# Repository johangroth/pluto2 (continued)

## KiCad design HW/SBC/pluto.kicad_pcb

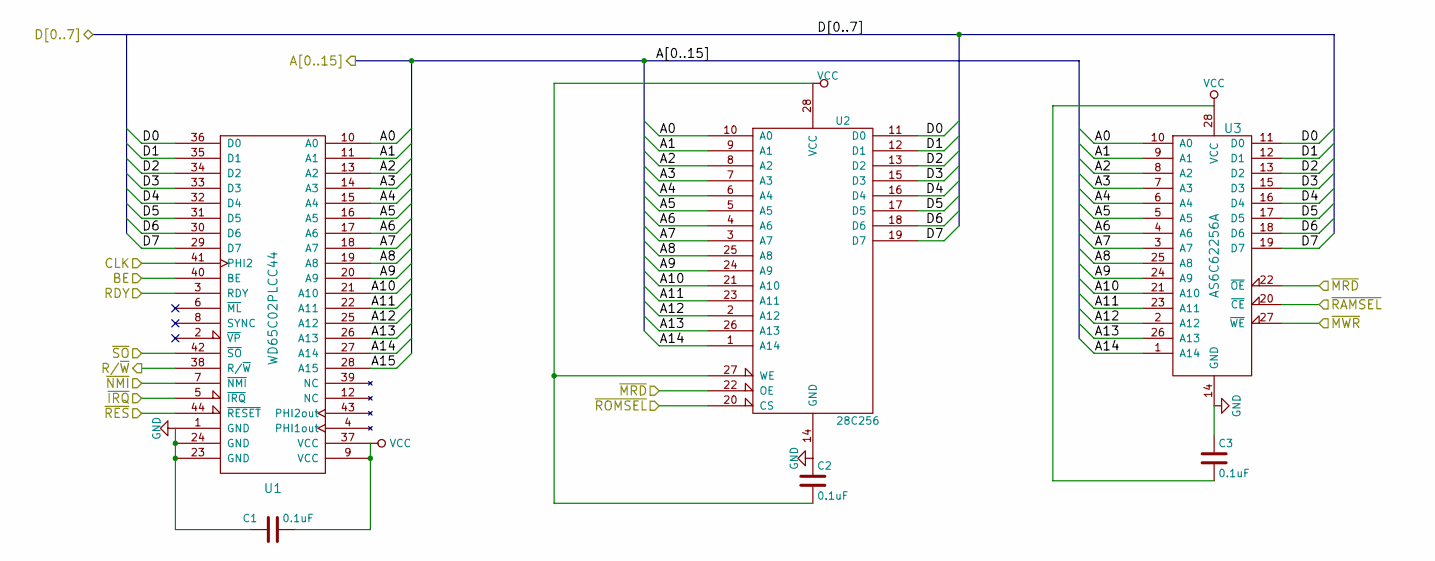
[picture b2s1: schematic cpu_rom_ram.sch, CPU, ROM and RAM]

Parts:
C1, C2, C3: 0.1uF; C_Disc_D4.7mm_W2.5mm_P5.00mm
U1: WD65C02PLCC44; PLCC-44_THT-Socket
U2: 28C256; DIP-28_W15.24mm_Socket
U3: AS6C62256A; DIP-28_W15.24mm_Socket

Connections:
/16bit IDE interface/A0: U1.10 (A0), U2.10 (A0), U3.10 (A0); also elsewhere on the board
/16bit IDE interface/A1: U1.11 (A1), U2.9 (A1), U3.9 (A1); also elsewhere on the board
/16bit IDE interface/A2: U1.13 (A2), U2.8 (A2), U3.8 (A2); also elsewhere on the board
/16bit IDE interface/D0: U1.36 (D0), U2.11 (D0), U3.11 (D0); also elsewhere on the board
/16bit IDE interface/D1: U1.35 (D1), U2.12 (D1), U3.12 (D1); also elsewhere on the board
/16bit IDE interface/D2: U1.34 (D2), U2.13 (D2), U3.13 (D2); also elsewhere on the board
/16bit IDE interface/D3: U1.33 (D3), U2.15 (D3), U3.15 (D3); also elsewhere on the board
/16bit IDE interface/D4: U1.32 (D4), U2.16 (D4), U3.16 (D4); also elsewhere on the board
/16bit IDE interface/D5: U1.31 (D5), U2.17 (D5), U3.17 (D5); also elsewhere on the board
/16bit IDE interface/D6: U1.30 (D6), U2.18 (D6), U3.18 (D6); also elsewhere on the board
/16bit IDE interface/D7: U1.29 (D7), U2.19 (D7), U3.19 (D7); also elsewhere on the board
/16bit IDE interface/~IRQ: U1.5 (~IRQ); also elsewhere on the board
/Address decoding and support section/A3: U1.14 (A3), U2.7 (A3), U3.7 (A3); also elsewhere on the board
/Address decoding and support section/A5: U1.16 (A5), U2.5 (A5), U3.5 (A5); also elsewhere on the board
/Address decoding and support section/A6: U1.17 (A6), U2.4 (A6), U3.4 (A6); also elsewhere on the board
/Address decoding and support section/A7: U1.18 (A7), U2.3 (A7), U3.3 (A7); also elsewhere on the board
/Address decoding and support section/A8: U1.19 (A8), U2.25 (A8), U3.25 (A8); also elsewhere on the board
/Address decoding and support section/A9: U1.20 (A9), U2.24 (A9), U3.24 (A9); also elsewhere on the board
/Address decoding and support section/A10: U1.21 (A10), U2.21 (A10), U3.21 (A10); also elsewhere on the board
/Address decoding and support section/A11: U1.22 (A11), U2.23 (A11), U3.23 (A11); also elsewhere on the board
/Address decoding and support section/A12: U1.25 (A12), U2.2 (A12), U3.2 (A12); also elsewhere on the board
/Address decoding and support section/A13: U1.26 (A13), U2.26 (A13), U3.26 (A13); also elsewhere on the board
/Address decoding and support section/A14: U1.27 (A14), U2.1 (A14), U3.1 (A14); also elsewhere on the board
/Address decoding and support section/A15: U1.28 (A15); also elsewhere on the board
/Address decoding and support section/BE: U1.40 (BE); also elsewhere on the board
/Address decoding and support section/CLK: U1.41 (PHI2); also elsewhere on the board
/Address decoding and support section/R/~W: U1.38 (R/~W); also elsewhere on the board
/Address decoding and support section/RDY: U1.3 (RDY); also elsewhere on the board
/Address decoding and support section/~MRD: U2.22 (OE), U3.22 (~OE); also elsewhere on the board
/Address decoding and support section/~MWR: U3.27 (~WE); also elsewhere on the board
/Address decoding and support section/~NMI: U1.7 (~NMI); also elsewhere on the board
/Address decoding and support section/~RAMSEL: U3.20 (~CE); also elsewhere on the board
/Address decoding and support section/~ROMSEL: U2.20 (CS); also elsewhere on the board
/Address decoding and support section/~SO: U1.42 (~SO); also elsewhere on the board
/CPU, ROM and RAM/A4: U1.15 (A4), U2.6 (A4), U3.6 (A4); also elsewhere on the board

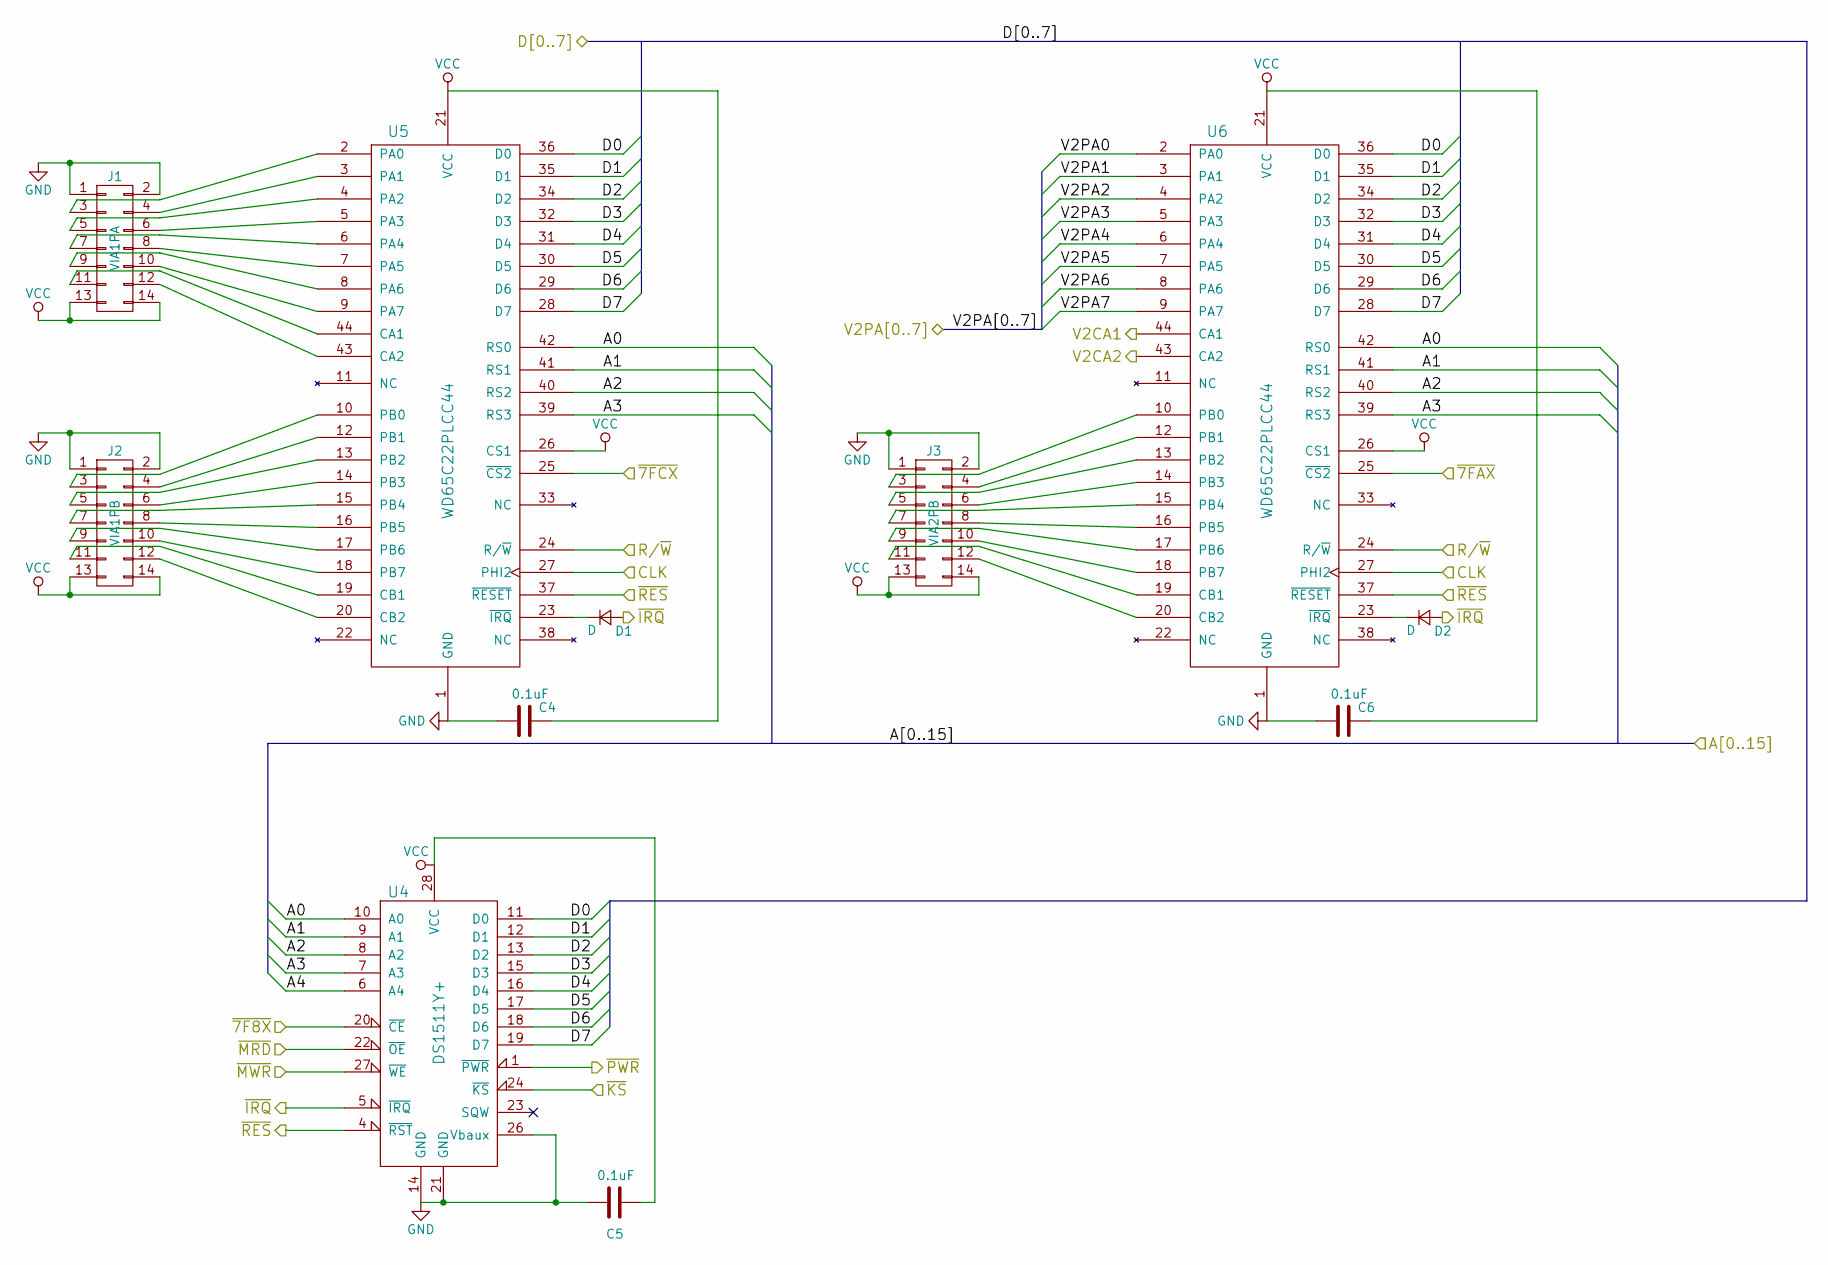
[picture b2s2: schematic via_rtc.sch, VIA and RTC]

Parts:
C4, C5, C6: 0.1uF; C_Disc_D4.7mm_W2.5mm_P5.00mm
D1, D2: D; D_DO-35_SOD27_P7.62mm_Horizontal
J1: VIA1PA; IDC-Header_2x07_Pitch2.54mm_Straight
J2: VIA1PB; IDC-Header_2x07_Pitch2.54mm_Straight
J3: VIA2PB; IDC-Header_2x07_Pitch2.54mm_Straight
U4: DS1511Y+; DIP-28_W15.24mm_Socket
U5, U6: WD65C22PLCC44; PLCC-44_THT-Socket

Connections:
/16bit IDE interface/A0: U4.10 (A0), U5.42 (RS0), U6.42 (RS0); also elsewhere on the board
/16bit IDE interface/A1: U4.9 (A1), U5.41 (RS1), U6.41 (RS1); also elsewhere on the board
/16bit IDE interface/A2: U4.8 (A2), U5.40 (RS2), U6.40 (RS2); also elsewhere on the board
/16bit IDE interface/D0: U4.11 (D0), U5.36 (D0), U6.36 (D0); also elsewhere on the board
/16bit IDE interface/D1: U4.12 (D1), U5.35 (D1), U6.35 (D1); also elsewhere on the board
/16bit IDE interface/D2: U4.13 (D2), U5.34 (D2), U6.34 (D2); also elsewhere on the board
/16bit IDE interface/D3: U4.15 (D3), U5.32 (D3), U6.32 (D3); also elsewhere on the board
/16bit IDE interface/D4: U4.16 (D4), U5.31 (D4), U6.31 (D4); also elsewhere on the board
/16bit IDE interface/D5: U4.17 (D5), U5.30 (D5), U6.30 (D5); also elsewhere on the board
/16bit IDE interface/D6: U4.18 (D6), U5.29 (D6), U6.29 (D6); also elsewhere on the board
/16bit IDE interface/D7: U4.19 (D7), U5.28 (D7), U6.28 (D7); also elsewhere on the board
/16bit IDE interface/~IRQ: D1.2 (A), D2.2 (A), U4.5 (~IRQ); also elsewhere on the board
/Address decoding and support section/A3: U4.7 (A3), U5.39 (RS3), U6.39 (RS3); also elsewhere on the board
/Address decoding and support section/CLK: U5.27 (PHI2), U6.27 (PHI2); also elsewhere on the board
/Address decoding and support section/R/~W: U5.24 (R/~W), U6.24 (R/~W); also elsewhere on the board
/Address decoding and support section/~7F8X: U4.20 (~CE); also elsewhere on the board
/Address decoding and support section/~7FAX: U6.25 (~CS2); also elsewhere on the board
/Address decoding and support section/~7FCX: U5.25 (~CS2); also elsewhere on the board
/Address decoding and support section/~KS: U4.24 (~KS); also elsewhere on the board
/Address decoding and support section/~MRD: U4.22 (~OE); also elsewhere on the board
/Address decoding and support section/~MWR: U4.27 (~WE); also elsewhere on the board
/Address decoding and support section/~PWR: U4.1 (~PWR); also elsewhere on the board
/CPU, ROM and RAM/A4: U4.6 (A4); also elsewhere on the board
unnamed: D1.1 (K), U5.23 (~IRQ)
unnamed: D2.1 (K), U6.23 (~IRQ)
unnamed: J1.3, U5.2 (PA0)
unnamed: J1.4, U5.3 (PA1)
unnamed: J1.5, U5.4 (PA2)
unnamed: J1.6, U5.5 (PA3)
unnamed: J1.7, U5.6 (PA4)
unnamed: J1.8, U5.7 (PA5)
unnamed: J1.9, U5.8 (PA6)
unnamed: J1.10, U5.9 (PA7)
unnamed: J1.11, U5.44 (CA1)
unnamed: J1.12, U5.43 (CA2)
unnamed: J2.3, U5.10 (PB0)
unnamed: J2.4, U5.12 (PB1)
unnamed: J2.5, U5.13 (PB2)
unnamed: J2.6, U5.14 (PB3)
unnamed: J2.7, U5.15 (PB4)
unnamed: J2.8, U5.16 (PB5)
unnamed: J2.9, U5.17 (PB6)
unnamed: J2.10, U5.18 (PB7)
unnamed: J2.11, U5.19 (CB1)
unnamed: J2.12, U5.20 (CB2)
unnamed: J3.3, U6.10 (PB0)
unnamed: J3.4, U6.12 (PB1)
unnamed: J3.5, U6.13 (PB2)
unnamed: J3.6, U6.14 (PB3)
unnamed: J3.7, U6.15 (PB4)
unnamed: J3.8, U6.16 (PB5)
unnamed: J3.9, U6.17 (PB6)
unnamed: J3.10, U6.18 (PB7)
unnamed: J3.11, U6.19 (CB1)
unnamed: J3.12, U6.20 (CB2)
unnamed 114: U6.2 (PA0); also elsewhere on the board
unnamed 115: U6.3 (PA1); also elsewhere on the board
unnamed 116: U6.4 (PA2); also elsewhere on the board
unnamed 117: U6.5 (PA3); also elsewhere on the board
unnamed 118: U6.6 (PA4); also elsewhere on the board
unnamed 119: U6.7 (PA5); also elsewhere on the board
unnamed 120: U6.8 (PA6); also elsewhere on the board
unnamed 121: U6.9 (PA7); also elsewhere on the board
unnamed 122: U6.44 (CA1); also elsewhere on the board
unnamed 123: U6.43 (CA2); also elsewhere on the board

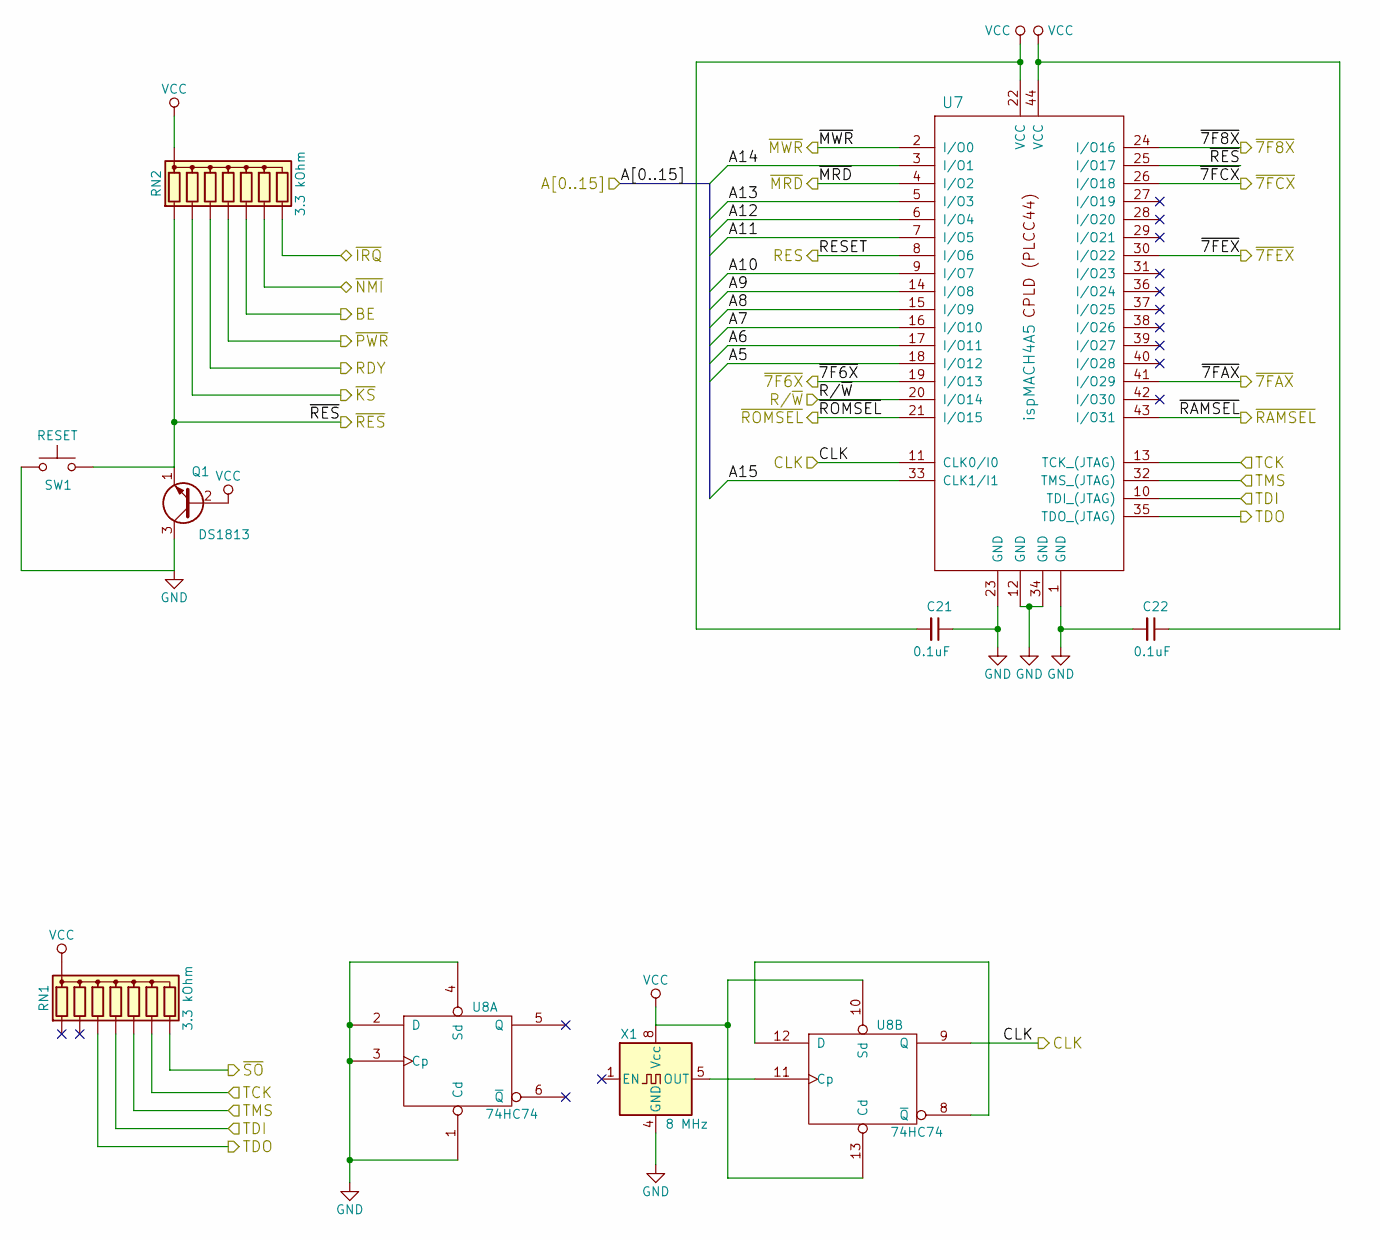
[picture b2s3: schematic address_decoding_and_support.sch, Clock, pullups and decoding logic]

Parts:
C21, C22: 0.1uF; C_Disc_D4.7mm_W2.5mm_P5.00mm
Q1: DS1813; TO-92_Inline_Narrow_Oval
RN1, RN2: 3.3 kOhm; R_Array_SIP8
SW1: RESET; SW_PUSH_6mm_h4.3mm
U7: ispMACH4A5; PLCC-44_THT-Socket
U8: 74HC74; DIP-14_W7.62mm_Socket
X1: 8 MHz; Oscillator_DIP-8

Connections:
/16bit IDE interface/FROM_CLK: U7.17 (I/O11); also elsewhere on the board
/16bit IDE interface/FROM_OE: U7.24 (I/O16); also elsewhere on the board
/16bit IDE interface/IDE_CS0: U7.19 (I/O13); also elsewhere on the board
/16bit IDE interface/OBT_OE: U7.20 (I/O14); also elsewhere on the board
/16bit IDE interface/TO_CLK: U7.30 (I/O22); also elsewhere on the board
/16bit IDE interface/TO_OE: U7.26 (I/O18); also elsewhere on the board
/16bit IDE interface/~IRQ: RN2.8 (R7); also elsewhere on the board
/Address decoding and support section/A3: U7.5 (I/O3); also elsewhere on the board
/Address decoding and support section/A5: U7.40 (I/O28); also elsewhere on the board
/Address decoding and support section/A6: U7.38 (I/O26); also elsewhere on the board
/Address decoding and support section/A7: U7.36 (I/O24); also elsewhere on the board
/Address decoding and support section/A8: U7.31 (I/O23); also elsewhere on the board
/Address decoding and support section/A9: U7.29 (I/O21); also elsewhere on the board
/Address decoding and support section/A10: U7.27 (I/O19); also elsewhere on the board
/Address decoding and support section/A11: U7.18 (I/O12); also elsewhere on the board
/Address decoding and support section/A12: U7.16 (I/O10); also elsewhere on the board
/Address decoding and support section/A13: U7.14 (I/O8); also elsewhere on the board
/Address decoding and support section/A14: U7.9 (I/O7); also elsewhere on the board
/Address decoding and support section/A15: U7.33 (CLK1/I1); also elsewhere on the board
/Address decoding and support section/BE: RN2.6 (R5); also elsewhere on the board
/Address decoding and support section/CLK: U7.11 (CLK0/I0), U8.9 (Q); also elsewhere on the board
/Address decoding and support section/R/~W: U7.7 (I/O5); also elsewhere on the board
/Address decoding and support section/RDY: RN2.4 (R3); also elsewhere on the board
/Address decoding and support section/RES: U7.37 (I/O25); also elsewhere on the board
/Address decoding and support section/TCK: RN1.7 (R6), U7.13 (TCK_(JTAG)); also elsewhere on the board
/Address decoding and support section/TDI: RN1.5 (R4), U7.10 (TDI_(JTAG)); also elsewhere on the board
/Address decoding and support section/TDO: RN1.4 (R3), U7.35 (TDO_(JTAG)); also elsewhere on the board
/Address decoding and support section/TMS: RN1.6 (R5), U7.32 (TMS_(JTAG)); also elsewhere on the board
/Address decoding and support section/~7F8X: U7.6 (I/O4); also elsewhere on the board
/Address decoding and support section/~7FAX: U7.2 (I/O0); also elsewhere on the board
/Address decoding and support section/~7FCX: U7.8 (I/O6); also elsewhere on the board
/Address decoding and support section/~7FEX: U7.3 (I/O1); also elsewhere on the board
/Address decoding and support section/~KS: RN2.3 (R2); also elsewhere on the board
/Address decoding and support section/~MRD: U7.41 (I/O29); also elsewhere on the board
/Address decoding and support section/~MWR: U7.43 (I/O31); also elsewhere on the board
/Address decoding and support section/~NMI: RN2.7 (R6); also elsewhere on the board
/Address decoding and support section/~PWR: RN2.5 (R4); also elsewhere on the board
/Address decoding and support section/~RAMSEL: U7.15 (I/O9); also elsewhere on the board
/Address decoding and support section/~ROMSEL: U7.21 (I/O15); also elsewhere on the board
/Address decoding and support section/~SO: RN1.8 (R7); also elsewhere on the board
unnamed: U8.11 (Cp), X1.5 (OUT)
unnamed: U8.8 (~Q), U8.12 (D)

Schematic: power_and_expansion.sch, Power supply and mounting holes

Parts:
J4: POWER; Molex_NanoFit_1x04x2.50mm_Angled
J8: JTAG; IDC-Header_2x05_Pitch2.54mm_Straight
J9: TEST_2P; Pin_Header_Straight_1x02_Pitch2.54mm
MK1, MK2, MK3, MK4, MK5, MK6: Mounting_Hole; MountingHole_3.2mm_M3_Pad

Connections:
/Address decoding and support section/TCK: J8.1; also elsewhere on the board
/Address decoding and support section/TDI: J8.5; also elsewhere on the board
/Address decoding and support section/TDO: J8.7; also elsewhere on the board
/Address decoding and support section/TMS: J8.3; also elsewhere on the board

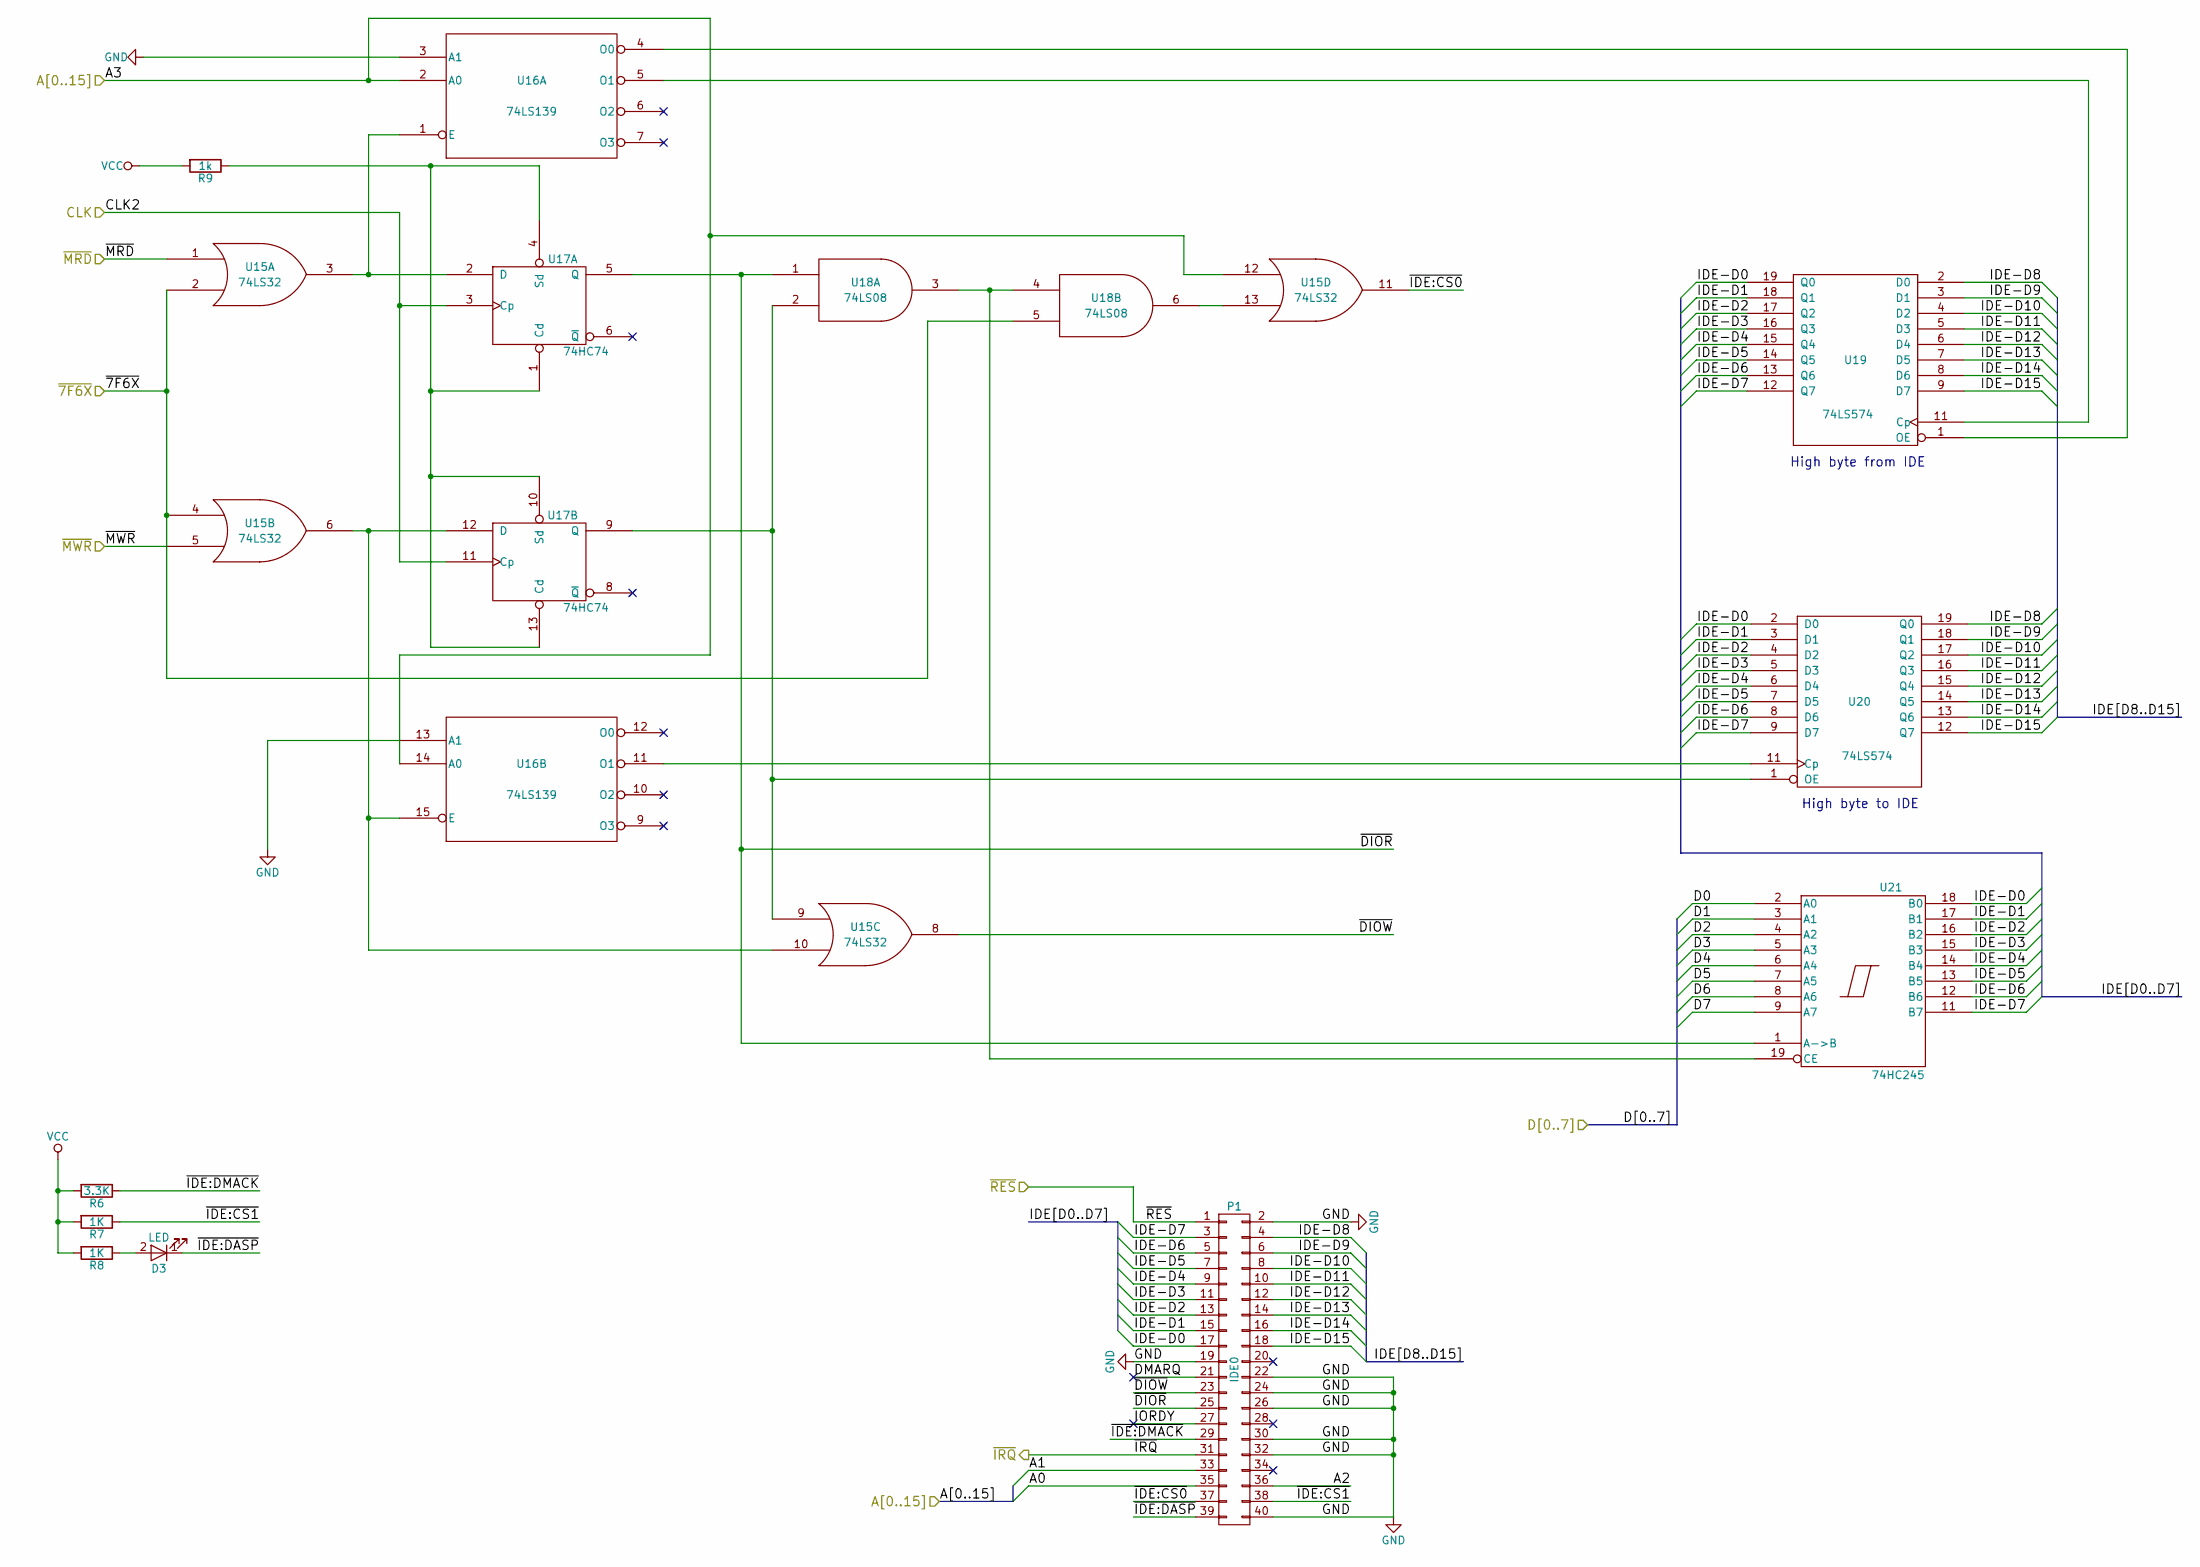
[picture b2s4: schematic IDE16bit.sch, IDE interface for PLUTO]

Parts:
D3: LED; LED_D3.0mm
P1: IDE0; IDC-Header_2x20_Pitch2.54mm_Straight
R6: 3.3K; R_Axial_DIN0411_L9.9mm_D3.6mm_P12.70mm_Horizontal
R7, R8: 1K; R_Axial_DIN0411_L9.9mm_D3.6mm_P12.70mm_Horizontal
R9: 1k; R_Axial_DIN0411_L9.9mm_D3.6mm_P12.70mm_Horizontal
U15: 74LS32; DIP-14_W7.62mm_Socket
U16: 74LS139; DIP-16_W7.62mm_Socket
U17: 74HC74; DIP-14_W7.62mm_Socket
U18: 74LS08; DIP-14_W7.62mm_Socket
U19, U20: 74LS574; DIP-20_W7.62mm_Socket
U21: 74HC245; DIP-20_W7.62mm_Socket

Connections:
/16bit IDE interface/A0: P1.35; also elsewhere on the board
/16bit IDE interface/A1: P1.33; also elsewhere on the board
/16bit IDE interface/A2: P1.36; also elsewhere on the board
/16bit IDE interface/D0: U21.2 (A0); also elsewhere on the board
/16bit IDE interface/D1: U21.3 (A1); also elsewhere on the board
/16bit IDE interface/D2: U21.4 (A2); also elsewhere on the board
/16bit IDE interface/D3: U21.5 (A3); also elsewhere on the board
/16bit IDE interface/D4: U21.6 (A4); also elsewhere on the board
/16bit IDE interface/D5: U21.7 (A5); also elsewhere on the board
/16bit IDE interface/D6: U21.8 (A6); also elsewhere on the board
/16bit IDE interface/D7: U21.9 (A7); also elsewhere on the board
/16bit IDE interface/FROM_CLK: U16.5 (O1), U19.11 (Cp); also elsewhere on the board
/16bit IDE interface/FROM_OE: U16.4 (O0), U19.1 (OE); also elsewhere on the board
/16bit IDE interface/IDE-D0: P1.17, U19.19 (Q0), U20.2 (D0), U21.18 (B0)
/16bit IDE interface/IDE-D1: P1.15, U19.18 (Q1), U20.3 (D1), U21.17 (B1)
/16bit IDE interface/IDE-D2: P1.13, U19.17 (Q2), U20.4 (D2), U21.16 (B2)
/16bit IDE interface/IDE-D3: P1.11, U19.16 (Q3), U20.5 (D3), U21.15 (B3)
/16bit IDE interface/IDE-D4: P1.9, U19.15 (Q4), U20.6 (D4), U21.14 (B4)
/16bit IDE interface/IDE-D5: P1.7, U19.14 (Q5), U20.7 (D5), U21.13 (B5)
/16bit IDE interface/IDE-D6: P1.5, U19.13 (Q6), U20.8 (D6), U21.12 (B6)
/16bit IDE interface/IDE-D7: P1.3, U19.12 (Q7), U20.9 (D7), U21.11 (B7)
/16bit IDE interface/IDE-D8: P1.4, U19.2 (D0), U20.19 (Q0)
/16bit IDE interface/IDE-D9: P1.6, U19.3 (D1), U20.18 (Q1)
/16bit IDE interface/IDE-D10: P1.8, U19.4 (D2), U20.17 (Q2)
/16bit IDE interface/IDE-D11: P1.10, U19.5 (D3), U20.16 (Q3)
/16bit IDE interface/IDE-D12: P1.12, U19.6 (D4), U20.15 (Q4)
/16bit IDE interface/IDE-D13: P1.14, U19.7 (D5), U20.14 (Q5)
/16bit IDE interface/IDE-D14: P1.16, U19.8 (D6), U20.13 (Q6)
/16bit IDE interface/IDE-D15: P1.18, U19.9 (D7), U20.12 (Q7)
/16bit IDE interface/IDE_CS0: P1.37, U15.11; also elsewhere on the board
/16bit IDE interface/OBT_OE: U18.3, U18.4, U21.19 (CE); also elsewhere on the board
/16bit IDE interface/TO_CLK: U16.11 (O1), U20.11 (Cp); also elsewhere on the board
/16bit IDE interface/TO_OE: U15.9, U17.9 (Q), U18.2, U20.1 (OE); also elsewhere on the board
/16bit IDE interface/~IDE:CS1: P1.38, R7.1
/16bit IDE interface/~IDE:DASP: D3.1 (K), P1.39
/16bit IDE interface/~IDE:DMACK: P1.29, R6.1
/16bit IDE interface/~IRQ: P1.31; also elsewhere on the board
unnamed: D3.2 (A), R8.1
unnamed: R9.1, U17.1 (Cd), U17.4 (Sd), U17.10 (Sd), U17.13 (Cd)
unnamed: U15.2, U15.4, U18.5
unnamed: U15.3, U16.1 (E), U17.2 (D)
unnamed: U15.6, U15.10, U16.15 (E), U17.12 (D)
unnamed: U15.12, U16.2 (A0), U16.14 (A0)
unnamed: U15.13, U18.6
unnamed: U17.3 (Cp), U17.11 (Cp)

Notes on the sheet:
High byte from IDE
High byte to IDE

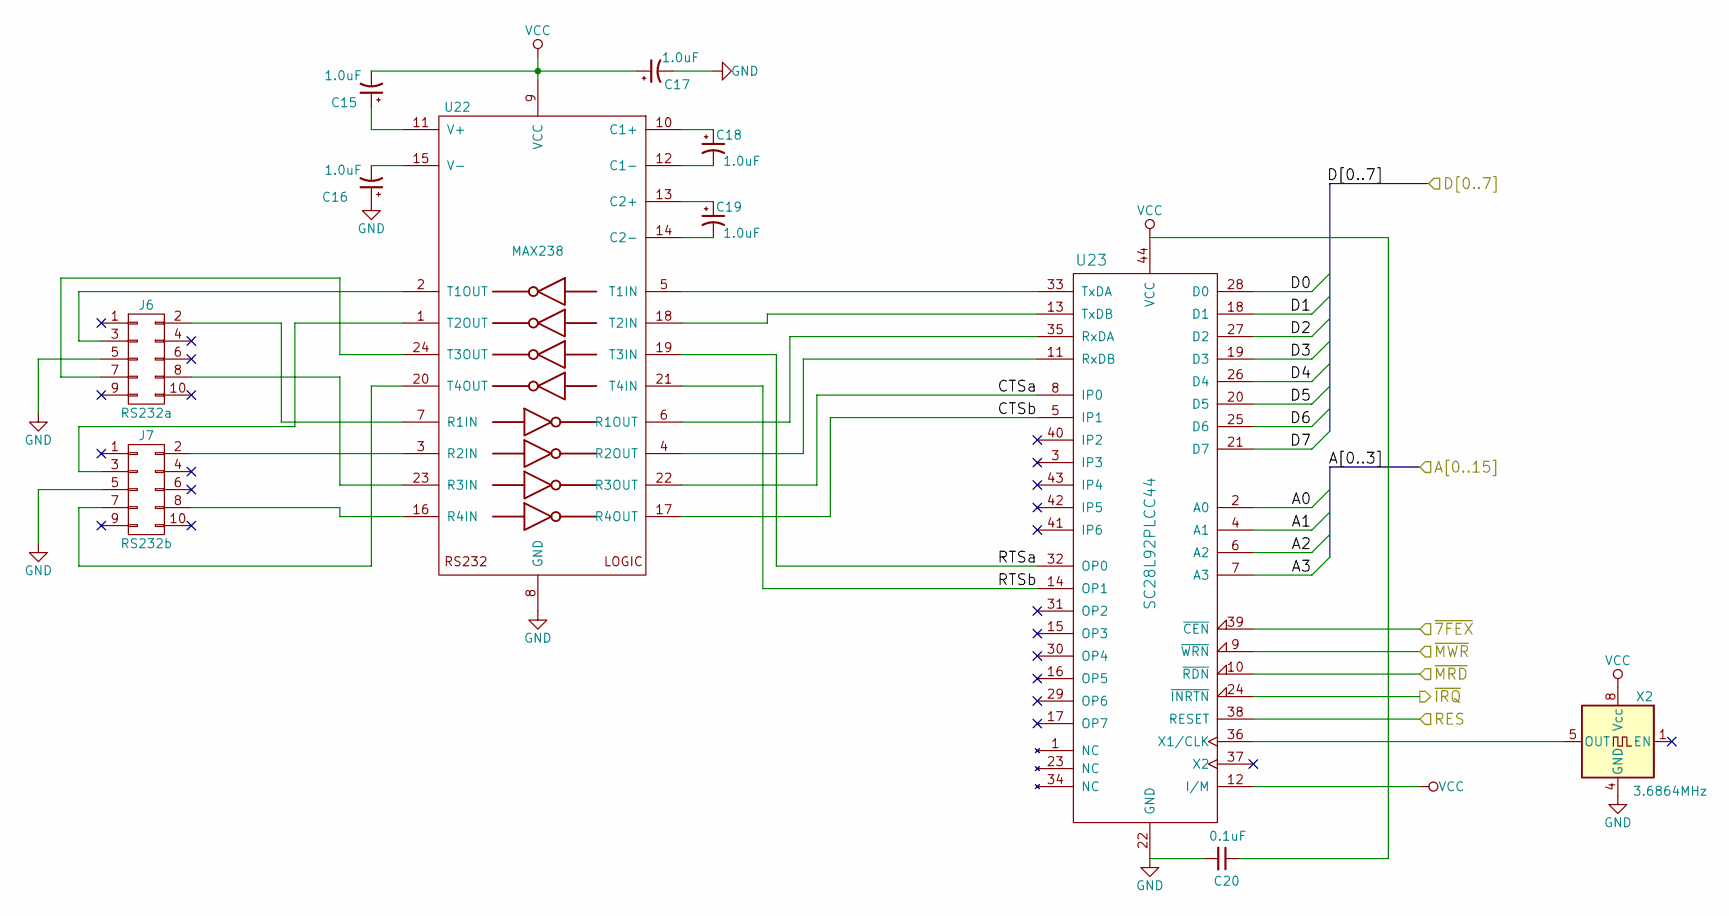
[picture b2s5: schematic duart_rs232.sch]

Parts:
C15, C16, C17, C18, C19: 1.0uF; CP_Radial_Tantal_D4.5mm_P2.50mm
C20: 0.1uF; C_Disc_D4.7mm_W2.5mm_P5.00mm
J6: RS232a; IDC-Header_2x05_Pitch2.54mm_Straight
J7: RS232b; IDC-Header_2x05_Pitch2.54mm_Straight
U22: MAX238; DIP-24_W7.62mm_Socket
U23: SC28L92PLCC44; PLCC-44_THT-Socket
X2: 3.6864MHz; Oscillator_DIP-8

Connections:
/16bit IDE interface/A0: U23.2 (A0); also elsewhere on the board
/16bit IDE interface/A1: U23.4 (A1); also elsewhere on the board
/16bit IDE interface/A2: U23.6 (A2); also elsewhere on the board
/16bit IDE interface/D0: U23.28 (D0); also elsewhere on the board
/16bit IDE interface/D1: U23.18 (D1); also elsewhere on the board
/16bit IDE interface/D2: U23.27 (D2); also elsewhere on the board
/16bit IDE interface/D3: U23.19 (D3); also elsewhere on the board
/16bit IDE interface/D4: U23.26 (D4); also elsewhere on the board
/16bit IDE interface/D5: U23.20 (D5); also elsewhere on the board
/16bit IDE interface/D6: U23.25 (D6); also elsewhere on the board
/16bit IDE interface/D7: U23.21 (D7); also elsewhere on the board
/16bit IDE interface/~IRQ: U23.24 (~INRTN); also elsewhere on the board
/Address decoding and support section/A3: U23.7 (A3); also elsewhere on the board
/Address decoding and support section/RES: U23.38 (RESET); also elsewhere on the board
/Address decoding and support section/~7FEX: U23.39 (~CEN); also elsewhere on the board
/Address decoding and support section/~MRD: U23.10 (~RDN); also elsewhere on the board
/Address decoding and support section/~MWR: U23.9 (~WRN); also elsewhere on the board
/DUART and RS232/CTSa: U22.22 (R3OUT), U23.8 (IP0)
/DUART and RS232/CTSb: U22.17 (R4OUT), U23.5 (IP1)
/DUART and RS232/RTSa: U22.19 (T3IN), U23.32 (OP0)
/DUART and RS232/RTSb: U22.21 (T4IN), U23.14 (OP1)
unnamed: C15.1, U22.11 (V+)
unnamed: C16.2, U22.15 (V-)
unnamed: C18.1, U22.10 (C1+)
unnamed: C18.2, U22.12 (C1-)
unnamed: C19.1, U22.13 (C2+)
unnamed: C19.2, U22.14 (C2-)
unnamed: J6.2, U22.7 (R1IN)
unnamed: J6.3, U22.2 (T1OUT)
unnamed: J6.7, U22.24 (T3OUT)
unnamed: J6.8, U22.23 (R3IN)
unnamed: J7.2, U22.3 (R2IN)
unnamed: J7.3, U22.1 (T2OUT)
unnamed: J7.7, U22.20 (T4OUT)
unnamed: J7.8, U22.16 (R4IN)
unnamed: U22.4 (R2OUT), U23.11 (RxDB)
unnamed: U22.5 (T1IN), U23.33 (TxDA)
unnamed: U22.6 (R1OUT), U23.35 (RxDA)
unnamed: U22.18 (T2IN), U23.13 (TxDB)
unnamed: U23.36 (X1/CLK), X2.5 (OUT)

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
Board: 4 copper layers, 55 parts (0 on the bottom side), 145 nets, no tracks yet.

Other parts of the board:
J5: VIA2PA; IDC-Header_2x07_Pitch2.54mm_Straight

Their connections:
unnamed 114: J5.3; also elsewhere on the board
unnamed 115: J5.4; also elsewhere on the board
unnamed 116: J5.5; also elsewhere on the board
unnamed 117: J5.6; also elsewhere on the board
unnamed 118: J5.7; also elsewhere on the board
unnamed 119: J5.8; also elsewhere on the board
unnamed 120: J5.9; also elsewhere on the board
unnamed 121: J5.10; also elsewhere on the board
unnamed 122: J5.11; also elsewhere on the board
unnamed 123: J5.12; also elsewhere on the board

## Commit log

2017-10-27 Initial commit for Pluto 2.0
2017-10-27 Moved datasheets to correct directory.
2017-10-27 Added readme
2017-12-11 Added CPLD to schematics. Updates rest of schematics to use CPLD
2017-12-11 Removed SW. Code is in PLUTO.
2017-12-11 Move SBC to root.
2017-12-19 Board ready for production. Added a reset IC that does both low and high logic RES. A power switch and fuse holder is in place. The expansion bus is back, but with an IDC 40 pin connector.
2017-12-19 Added datasheets for voltage regulator and power switch. Added footprint for power switch. Added gerbers files for VCC and GND planes.
2017-12-19 DRC says for pins are not connect. Should that be the case, it can be rectified after production.
2017-12-20 Update of Gerbers files after comments from Newbury Electronics.
2017-12-22 Final touches for PCB train web service.
2017-12-24 Added address decoding in ABEL (accidentally deleted the schmatic version).
2017-12-24 Address decoding done.
2017-12-26 Fixed bug in address decoding (found in simulation).
2018-01-22 Small changes
2018-02-01 Beginning to link ABEL with schematics.
2018-02-01 Remove X bit on text files
2018-02-13 Added full address decoding as a schematic. DRC fails.
2018-02-19 CPLD schematic updates.
2018-02-19 CPLD schematic changes.
2018-06-30 Added PlutoDos so support for NXP SC28L92 can be added.
2018-06-30 Preparing BIOS for new serial communication device, SC28L92.
2018-06-30 ctags not used by atom so removed. Some code cleanup.
2018-06-30 Just update of tags.
2018-07-30 Document/HOWTO program SC28L92.
2018-08-16 Preparation for using SC28L92 DUART as a communication device.
2018-08-22 Started developing the ISR for the DUART.
2018-08-23 Added some more code to DUART ISR
2018-08-23 Added send/receive code in ISR. Doesn't handle TxFIFOA full condition.
2018-09-30 Test code. Should blink a LED connected to VIA PB0 but doesn't.
2018-11-15 Via1 io $7fa0 Via2 io $7fc0 Fix bug in delay routine. Use temp1 in monitor instead of tmp used in ide routines.
2019-05-05 Small changes to schematics
2019-07-19 Various changes
2019-08-05 Preparation for Pluto v3.0
2019-08-05 A better layout of PCB.
2019-08-06 Autorouting of Pluto v3.0 complete. Fixed VCC/GND and IDE-A2(!)
2019-08-06 Various changes.
2019-08-06 Added Atom tags file
2019-09-07 Converting to SMD of almost all components.
2019-09-19 New PCB layout is taking shape.
2019-09-19 Added new datasheet for SMD resistor bus array.
2019-09-20 Added datasheets for 7-seg LED Kingbright displays.
2019-09-25 Added Arduino sketch to debug pluto. Added IDE spec.
2019-09-29 Faulty PSU didn't give board enough voltage, hence never started. Plus blunder with power on LED.
2019-09-29 KiCad updated schematics
2019-09-29 Added some new files
2019-09-29 Layout of PCB continues.
2019-09-30 Added de-coupling cap to 74hc74. Rearranged PCB a bit.
2019-10-20 Pluto2 V3 PCB routed and finished. Removed all Pluto2 V2 Gerber files. Add GAL files for address and IO decoding.
2019-10-21 Beginning of conversion to ca65.
2019-10-21 Still a lot of assembly errors.
2019-10-22 More assembly errors fixed.
2019-11-03 Added clock generator using an Arduino Nano. Gerbers made and sent to manufacturer. Some assembler testing bread board setup
2019-11-12 Added comments.
2019-11-13 Added monitor command L to disassemble code. Some zp.inc clean up.
2019-11-14 Beginning to add real support for SC28L92
2019-11-14 Directory restructoring
2019-11-16 Sped up blinking of LED.
2019-11-19 Using BDD's receive with FIFO ISR. CHIN_no_wait is default and the only input routine. Updates to both BIOS (read_line, read_char, et.al) have still to be done. CHOUT still needs to be rewritten to t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
2019-11-23 Send an A to DUART channel A as a test.
2019-12-11 Changes to duart code.
2019-12-17 Added some algorithms. Some restructuring of directories.
2019-12-17 Added files forgotten previous commit.
2019-12-17 Added sw_stack as an implementation example of a data stack not using ZP (not tested).
2020-02-27 Some white space removal.
2020-03-08 Fixing setup of SC28L92. Still WIP.
2020-03-09 Disable power down. Align init code to force a page break when reading the init table.
2020-03-10 Make sure a page break happens.
2020-03-11 Indirect addressing when writing to SC28L92 registers.
2020-05-09 New version of SC28L92 initialisation. Still WIP (ie, doesn't work)
2020-05-09 KiCad added this file.
2020-12-06 Input/output at 115000 kbps works (required a MAX238).
2020-12-06 Added some comments.
2020-12-06 Use SC28L92 instead of ST16C550.
2020-12-25 Add send/receive procs.
2021-07-25 New version with a TL16C550 UART
2021-08-14 small updates
2021-08-14 16C550 code from ancientcomputing/rc2014.
